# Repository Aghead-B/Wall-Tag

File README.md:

# Walltag

Looking for the prototype files? They can be found in the 'prototype' branch.

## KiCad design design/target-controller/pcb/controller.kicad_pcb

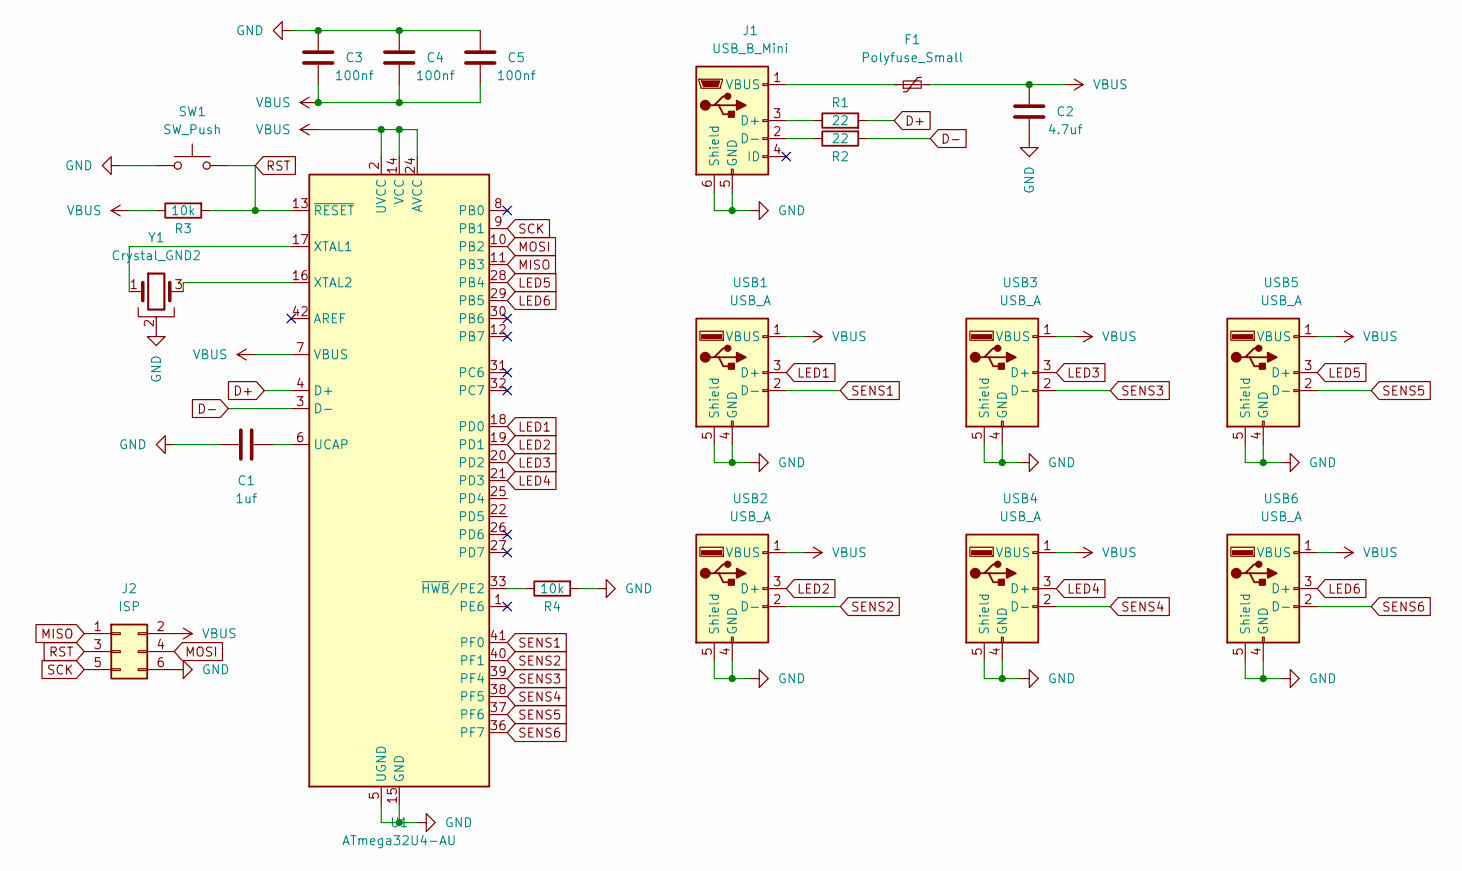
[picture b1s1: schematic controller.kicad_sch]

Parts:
C1: 1uf; C_0805_2012Metric_Pad1.15x1.40mm_HandSolder
C2: 4.7uf; C_0805_2012Metric_Pad1.15x1.40mm_HandSolder
C3, C4, C5: 100nf; C_0805_2012Metric_Pad1.15x1.40mm_HandSolder
F1: Polyfuse_Small; R_0805_2012Metric_Pad1.15x1.40mm_HandSolder
J1: USB_B_Mini; U-M-M5DD-W-1
J2: ISP; isp_standard
R1, R2: 22; R_0805_2012Metric_Pad1.15x1.40mm_HandSolder
R3, R4: 10k; R_0805_2012Metric_Pad1.15x1.40mm_HandSolder
SW1: SW_Push; SW_SPST_TL3342
U1: ATmega32U4-AU; TQFP-44_10x10mm_P0.8mm
USB1, USB2, USB3, USB4, USB5, USB6: USB_A; U-A-24DD-Y-1
Y1: Crystal_GND2; Resonator_SMD_muRata_CSTNExxV-3Pin-p1.2

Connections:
D+: R1.2, U1.4 (D+)
D-: R2.2, U1.3 (D-)
GND: C1.2, C2.2, C3.1, C4.1, C5.1, J1.5 (GND), J1.6 (Shield), J2.6, R4.2, SW1.1, U1.5 (UGND), U1.15 (GND), U1.23 (GND), U1.35 (GND), U1.43 (GND), USB1.4 (GND), USB1.5 (Shield), USB2.4 (GND), USB2.5 (Shield), USB3.4 (GND), USB3.5 (Shield), USB4.4 (GND), USB4.5 (Shield), USB5.4 (GND), USB5.5 (Shield), USB6.4 (GND), USB6.5 (Shield), Y1.2
LED1: U1.18 (PD0), USB1.3 (D+)
LED2: U1.19 (PD1), USB2.3 (D+)
LED3: U1.20 (PD2), USB3.3 (D+)
LED4: U1.21 (PD3), USB4.3 (D+)
LED5: U1.28 (PB4), USB5.3 (D+)
LED6: U1.29 (PB5), USB6.3 (D+)
MISO: J2.1, U1.11 (PB3)
MOSI: J2.4, U1.10 (PB2)
unnamed: C1.1, U1.6 (UCAP)
unnamed: F1.1, J1.1 (VBUS)
unnamed: J1.2 (D-), R2.1
unnamed: J1.3 (D+), R1.1
unnamed: R4.1, U1.33 (~HWB~/PE2)
unnamed: U1.17 (XTAL1), Y1.1
unnamed: U1.16 (XTAL2), Y1.3
RST: J2.3, R3.2, SW1.2, U1.13 (~RESET)
SCK: J2.5, U1.9 (PB1)
SENS1: U1.41 (PF0), USB1.2 (D-)
SENS2: U1.40 (PF1), USB2.2 (D-)
SENS3: U1.39 (PF4), USB3.2 (D-)
SENS4: U1.38 (PF5), USB4.2 (D-)
SENS5: U1.37 (PF6), USB5.2 (D-)
SENS6: U1.36 (PF7), USB6.2 (D-)
VBUS: C2.1, C3.2, C4.2, C5.2, F1.2, J2.2, R3.1, U1.2 (UVCC), U1.7 (VBUS), U1.14 (VCC), U1.24 (AVCC), U1.34 (VCC), U1.44 (AVCC), USB1.1 (VBUS), USB2.1 (VBUS), USB3.1 (VBUS), USB4.1 (VBUS), USB5.1 (VBUS), USB6.1 (VBUS)

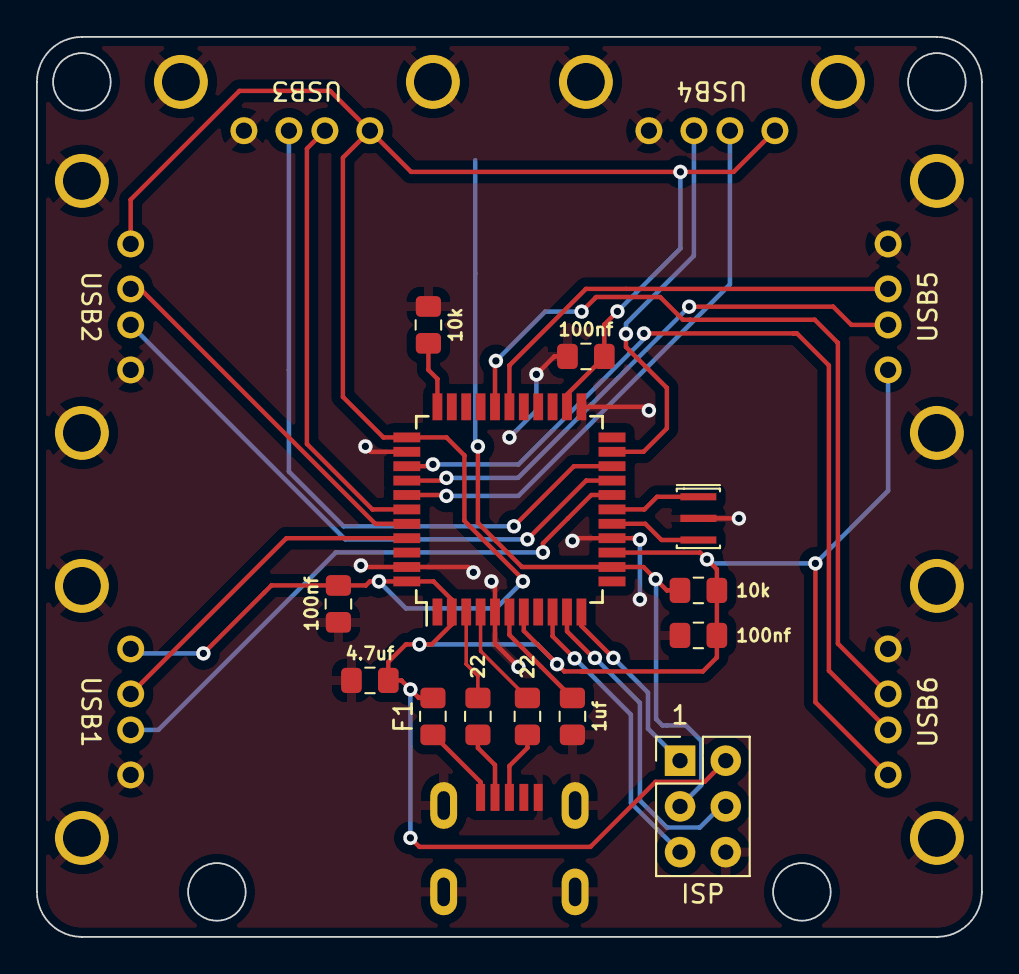
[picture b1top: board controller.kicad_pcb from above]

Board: 2 copper layers, 52.5 x 50.0 mm, 21 parts (1 on the bottom side), 27 nets.

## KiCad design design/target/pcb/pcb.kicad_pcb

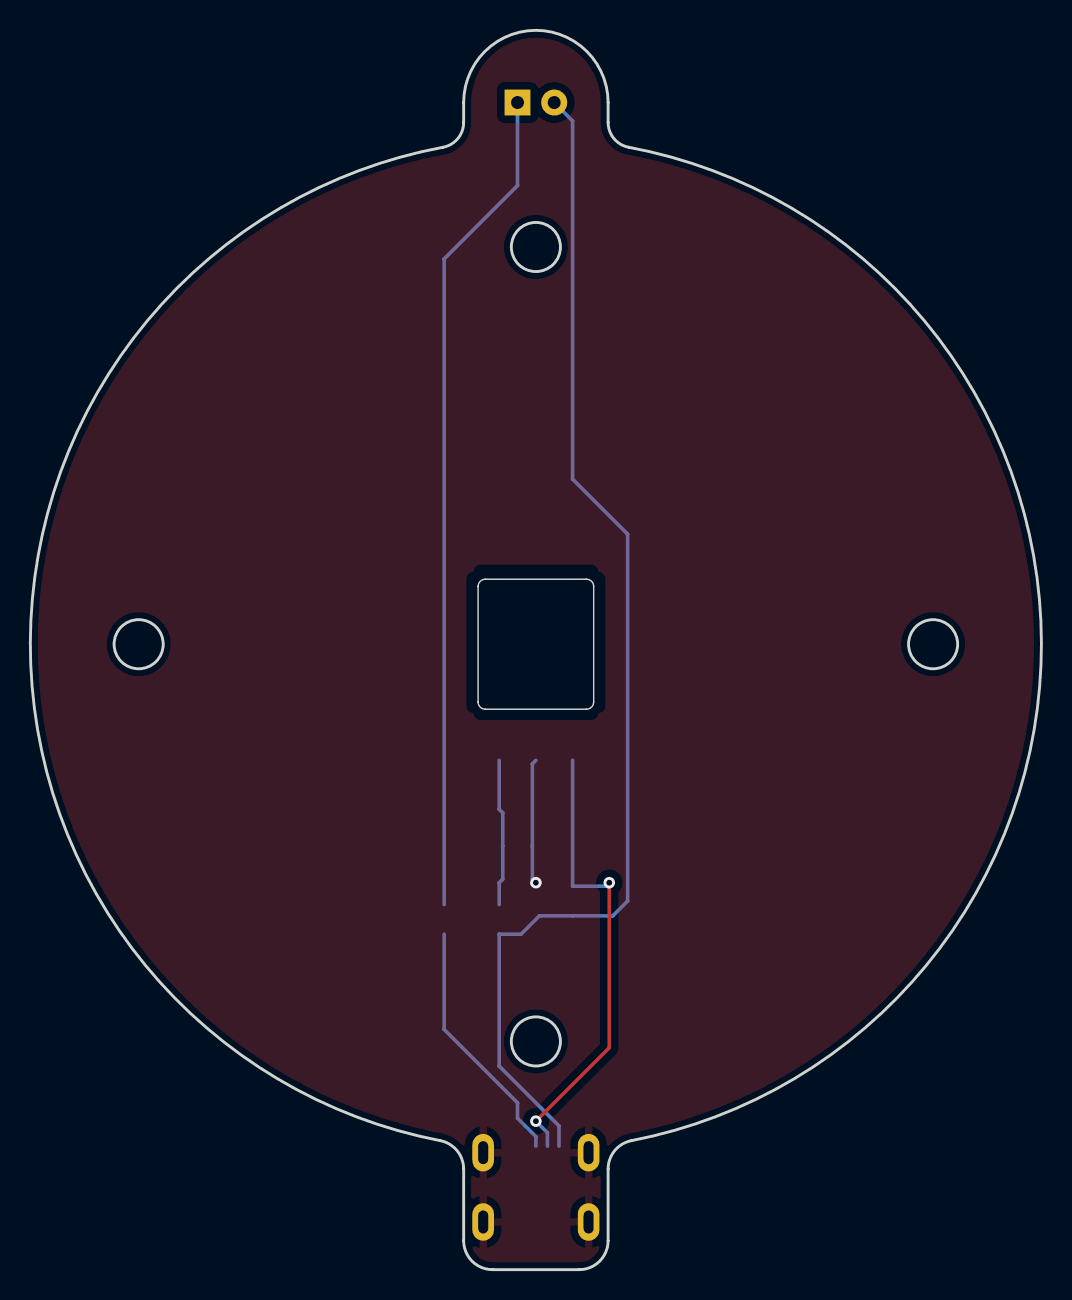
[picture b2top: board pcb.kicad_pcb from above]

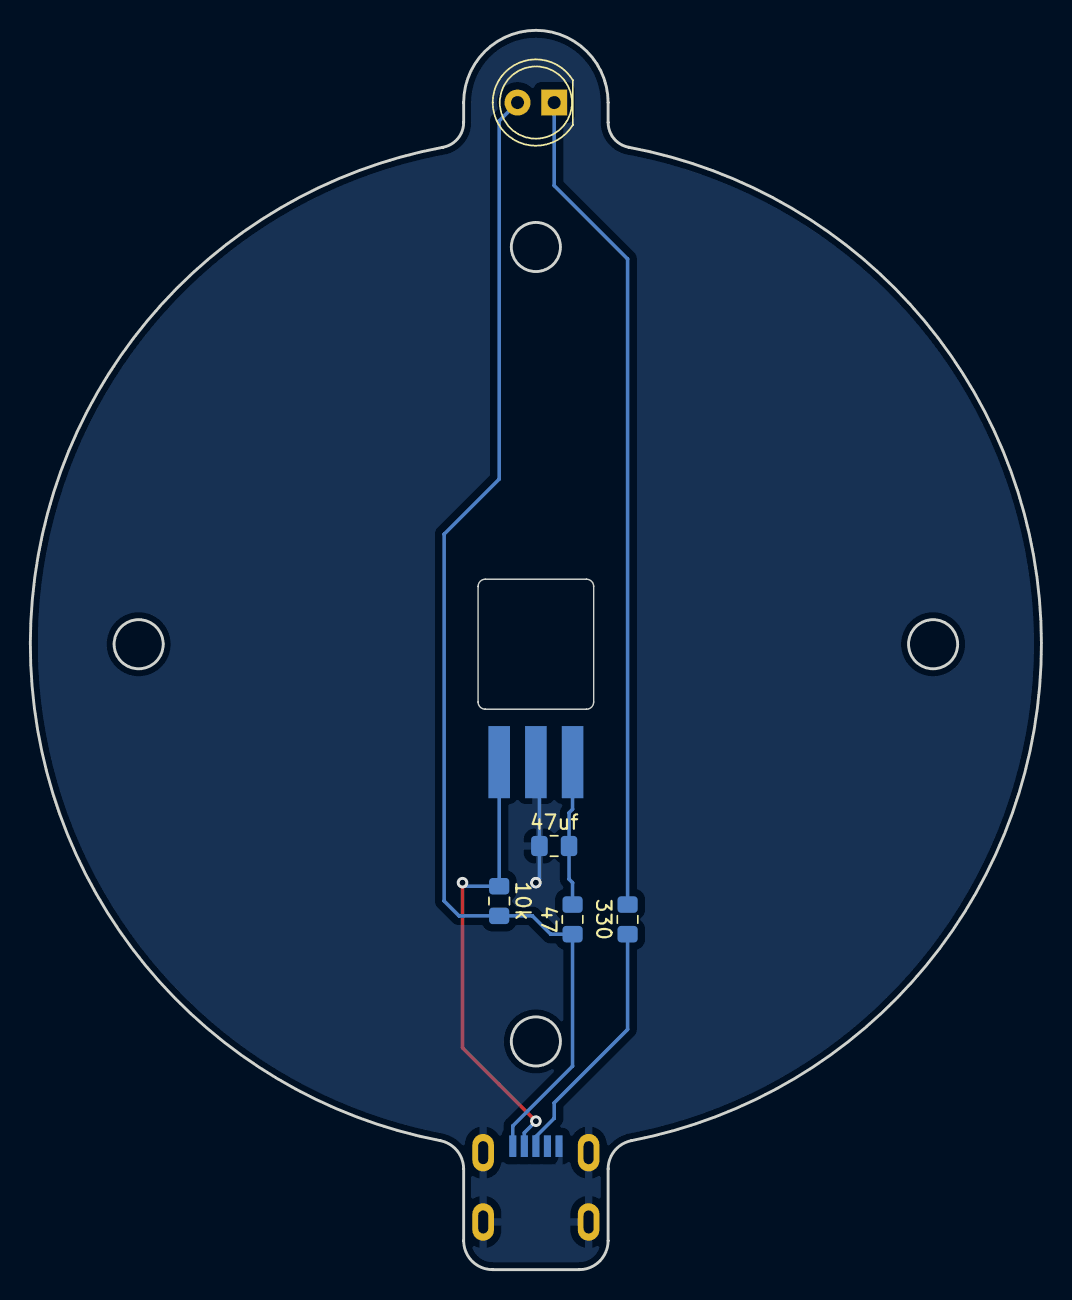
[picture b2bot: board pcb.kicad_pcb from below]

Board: 2 copper layers, 70.0 x 85.8 mm, 7 parts (7 on the bottom side), 6 nets.

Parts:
C1: 47uf; C_0805_2012Metric_Pad1.15x1.40mm_HandSolder
D1: LED; LED_D5.0mm
J1: USB_B_Mini; U-M-M5DD-W-1
R1: 47; R_0805_2012Metric_Pad1.15x1.40mm_HandSolder
R2: 10k; R_0805_2012Metric_Pad1.15x1.40mm_HandSolder
R3: 330; R_0805_2012Metric_Pad1.15x1.40mm_HandSolder
U1: IR_HX1838; ir_sensor

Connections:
GND: C1.2, J1.5 (GND), J1.6 (Shield), U1.2 (GND)
LED: J1.3 (D+), R3.2
unnamed: C1.1, R1.1, U1.3 (VCC)
unnamed: D1.1 (K), R3.1
SIGNAL: J1.2 (D-), R2.2, U1.1 (SIGNAL)
VCC: D1.2 (A), J1.1 (VBUS), R1.2, R2.1

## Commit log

2020-10-21 Upload prototype gun/target files
2020-10-21 Upload New File
2020-10-23 Game Files
2020-10-23 Upload files
2020-10-24 Class based code!
2020-10-25 update game
2020-10-25 Add testmode to game
2020-10-26 Replace index.html
2020-10-26 Replace Game.py
2020-10-26 Replace web.py
2020-11-24 Upload begin website
2020-11-24 upload target design
2020-11-24 Upload target pcb/case
2020-11-25 Move static files to folder, improve html drastically
2020-11-25 replace line breaks with paragraphs
2020-11-26 Website aangepast
2020-12-01 Target controller PCB design
2020-12-08 edit database
2020-12-08 Cleanup
2020-12-08 wat kleine aanpassingen in html en web.py voor json ondersteuning
2020-12-08 Code voor de Targets
2020-12-08 Upload database code
2020-12-09 database update
2020-12-13 Database Done
2020-12-14 Geupdated Guncode
2020-12-17 Update PCBs
2020-12-17 Move arduino code/update pins
2020-12-19 Upload gun design/update target design
2020-12-28 Add new directory
2020-12-28 Console design in fushion
2020-12-28 da new change
2020-12-28 Console 2.0
2020-12-29 2e verandering met lastLine en automatische stop
2020-12-31 halleffect code
2021-01-01 Monitoring
2021-01-03 Semi-final version of Walltag
2021-01-07 Add hall effect sensor
2021-01-07 Allow hall effect sensing before target/gun
2021-01-11 Add hall effect/distance sensor check to game
2021-01-11 Remove old files, update all designs and update web pages
2021-01-11 Remove kicad backup files
2021-01-11 Update gitignore file
2021-01-14 Update templates
2021-01-14 comments
2021-01-19 Last few fixes
2021-01-19 Remove redundant code
2021-01-19 More removal of redundant code
